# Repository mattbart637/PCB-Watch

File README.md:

# PCB Watch

A digital watch with a PIC16 and 4-digit segmented LCD display on a 2-layer PCB. It's my first microcontroller project outside the Arduino environment and the smallest SMT soldering I've done to date.

This build was heavily inspired by [Joe Sullivan's take](http://joesul.li/van/watch/) on a PIC16 watch. I loved finished look but didn't trust my soldering skills for the tiny hall-effect sensor or the daughter board it mounts on. Instead I simplified the interface to a single push-button. It makes the hardware simpler, but the firmware took a while to wrap my head around. 

I designed it for Seiko NH35 watch cases that accept 29mm dials, mostly because the NH35 has a strong modding community and there's plenty of aftermarket cases available. I got mine on AliExpress for under $20. A pair of 3D-printed spacers completes the build.

# Specs

| | |
| --- | --- |
| Dimensions | 29mm diameter, 7mm thick |
| Accuracy | 0.43 seconds/day, ~5 PPM |
| Current draw | 28.5µA @ 3V |
| Battery type | CR1220 |
| Runtime on 40mAh battery | ~58 days (estimate) |

# How to Use 

Once you insert a CR1220 battery it starts keeping time from 12:00.

1. Press and hold the button until Decimal Point 3 (DP3) lights up. Short press the button to change the minute.
2. Press and hold again and Decimal Point 1 (DP1) will light instead. Short press the button to change the hour.
3. Press and hold a final time until the decimal point turns off, setting the time.

# Photos

# Improvements for v2

My biggest gripe by far is with the 3D printed spacers, which work well but are tricky prints. I didn't include any anti-rotation features on the board, so instead the spacers have tiny pegs that sit in the programming header through holes. The parts aren't well suited to an FDM printer; mine were done on a DLP resin machine.

The spacer has a small tab that sticks into the crown opening to stop it rotating within the watch case. It works on the watch case I'm using (though not on all the ones I've tried) but blocks access to the button. That means disassembling the watch to set the time. Maybe not a huge deal since the battery life is only ~2 months, but I'd do it differently next time.

I want to make the spacers less demanding prints and include a keying tab on the board itself. I'd also swap the button with an edge-mount one (that sits in a recess on the board) to bring it more in line with the crown. Preferably one with a more tactile feel too.

Some other things I'd change:
- Add 24-Hour time support 
- I think there's room for reducing the current consumption and extending the battery life further.
- The manufacturer's footprint for the battery holder has the ground pad smaller than the battery diameter. On the next rev I'd make the pad larger than the battery diameter to get better contact. Otherwise you have to flood the pad with solder (making it higher than the surrounding soldermask) to make contact.

# Credits & References

Joe Sullivan's PIC16 watch: <http://joesul.li/van/watch/>

NH35 Specifications: <https://www.timemodule.com/uploads/attachments/download/Spec%20Sheet/NH35_SS.pdf>

It's not the same implementation or even the same microcontroller I used, but Microchip's Yet Another Clock Featuring the PIC16C924 application note was very helpful: <https://www.microchip.com/en-us/application-notes/an649>

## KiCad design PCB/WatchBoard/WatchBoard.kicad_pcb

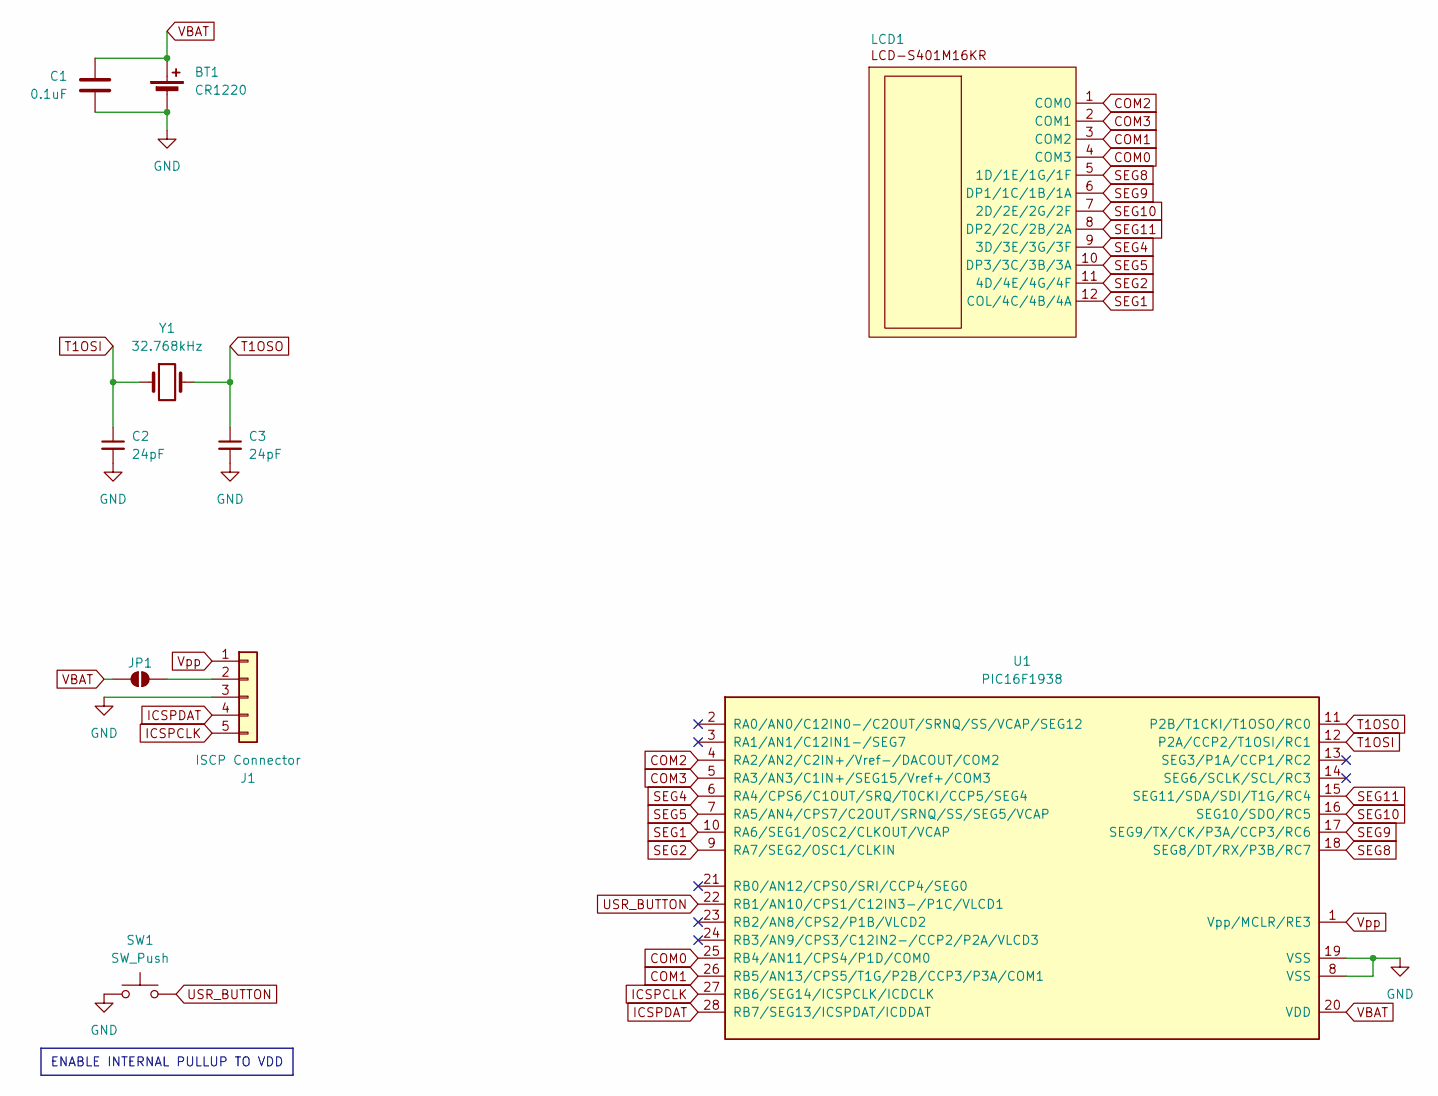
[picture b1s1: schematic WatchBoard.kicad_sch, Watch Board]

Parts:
BT1: CR1220; keystone_PN2894_BatteryHolder; Part_Number 2894
C1: 0.1uF; C_1206_3216Metric_Pad1.33x1.80mm_HandSolder; Part_Number C1206C104K5RACTU
C2, C3: 24pF; C_1206_3216Metric_Pad1.33x1.80mm_HandSolder; Part_Number C1206C240F1HACTU
J1: ISCP Connector; ISCPHeader_1x05_P2.54mm
JP1: SolderJumper-2_P1.3mm_Open_TrianglePad1.0x1.5mm
LCD1: LCD-S401M16KR; Part_Number LCD-S401M16KR
SW1: SW_Push; SW_B3U-3000P-B_OMR; Part_Number B3U-3000P-B
U1: PIC16F1938; PIC16F1938-X&slash_SS_MCH-L; Part_Number PIC16F1938T-I/SS
Y1: 32.768kHz; Crystal_CFS-206_D2.0mm_L6.2mm; Part_Number CFS-20632768HZFB

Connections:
COM0: LCD1.4 (COM3), U1.25 (RB4/AN11/CPS4/P1D/COM0)
COM1: LCD1.3 (COM2), U1.26 (RB5/AN13/CPS5/T1G/P2B/CCP3/P3A/COM1)
COM2: LCD1.1 (COM0), U1.4 (RA2/AN2/C2IN+/Vref-/DACOUT/COM2)
COM3: LCD1.2 (COM1), U1.5 (RA3/AN3/C1IN+/SEG15/Vref+/COM3)
GND: BT1.2 (-), C1.2, C2.2, C3.2, J1.3, SW1.2, U1.8 (VSS), U1.19 (VSS)
ICSPCLK: J1.5, U1.27 (RB6/SEG14/ICSPCLK/ICDCLK)
ICSPDAT: J1.4, U1.28 (RB7/SEG13/ICSPDAT/ICDDAT)
unnamed: J1.2, JP1.2 (B)
SEG1: LCD1.12 (COL/4C/4B/4A), U1.10 (RA6/SEG1/OSC2/CLKOUT/VCAP)
SEG2: LCD1.11 (4D/4E/4G/4F), U1.9 (RA7/SEG2/OSC1/CLKIN)
SEG4: LCD1.9 (3D/3E/3G/3F), U1.6 (RA4/CPS6/C1OUT/SRQ/T0CKI/CCP5/SEG4)
SEG5: LCD1.10 (DP3/3C/3B/3A), U1.7 (RA5/AN4/CPS7/C2OUT/SRNQ/SS/SEG5/VCAP)
SEG8: LCD1.5 (1D/1E/1G/1F), U1.18 (SEG8/DT/RX/P3B/RC7)
SEG9: LCD1.6 (DP1/1C/1B/1A), U1.17 (SEG9/TX/CK/P3A/CCP3/RC6)
SEG10: LCD1.7 (2D/2E/2G/2F), U1.16 (SEG10/SDO/RC5)
SEG11: LCD1.8 (DP2/2C/2B/2A), U1.15 (SEG11/SDA/SDI/T1G/RC4)
T1OSI: C2.1, U1.12 (P2A/CCP2/T1OSI/RC1), Y1.1
T1OSO: C3.1, U1.11 (P2B/T1CKI/T1OSO/RC0), Y1.2
USR_BUTTON: SW1.1, U1.22 (RB1/AN10/CPS1/C12IN3-/P1C/VLCD1)
VBAT: BT1.1 (+), C1.1, JP1.1 (A), U1.20 (VDD)
Vpp: J1.1, U1.1 (Vpp/MCLR/RE3)

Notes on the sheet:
ENABLE INTERNAL PULLUP TO VDD

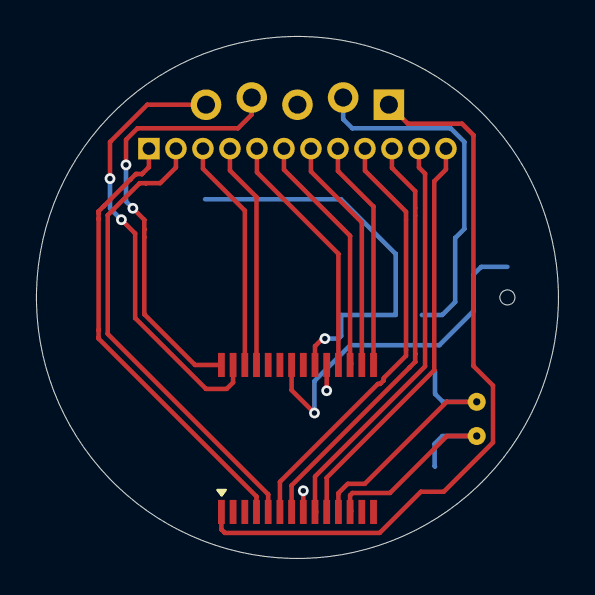
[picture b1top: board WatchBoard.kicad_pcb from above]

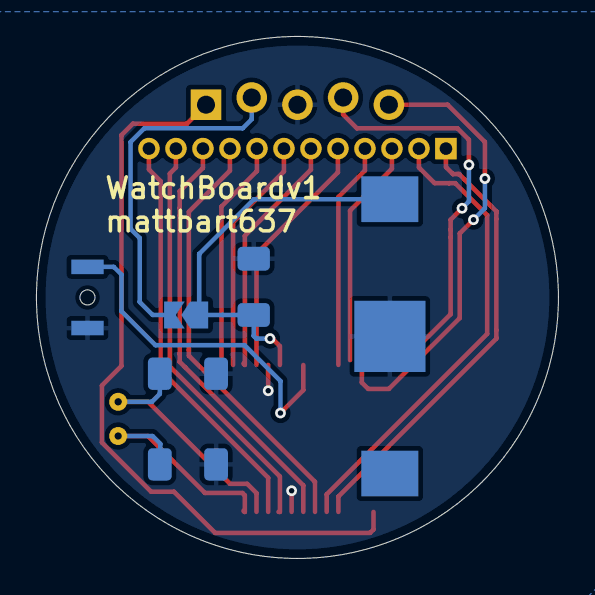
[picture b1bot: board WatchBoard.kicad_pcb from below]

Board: 2 copper layers, 29.0 x 29.0 mm, 10 parts (7 on the bottom side), 21 nets.
